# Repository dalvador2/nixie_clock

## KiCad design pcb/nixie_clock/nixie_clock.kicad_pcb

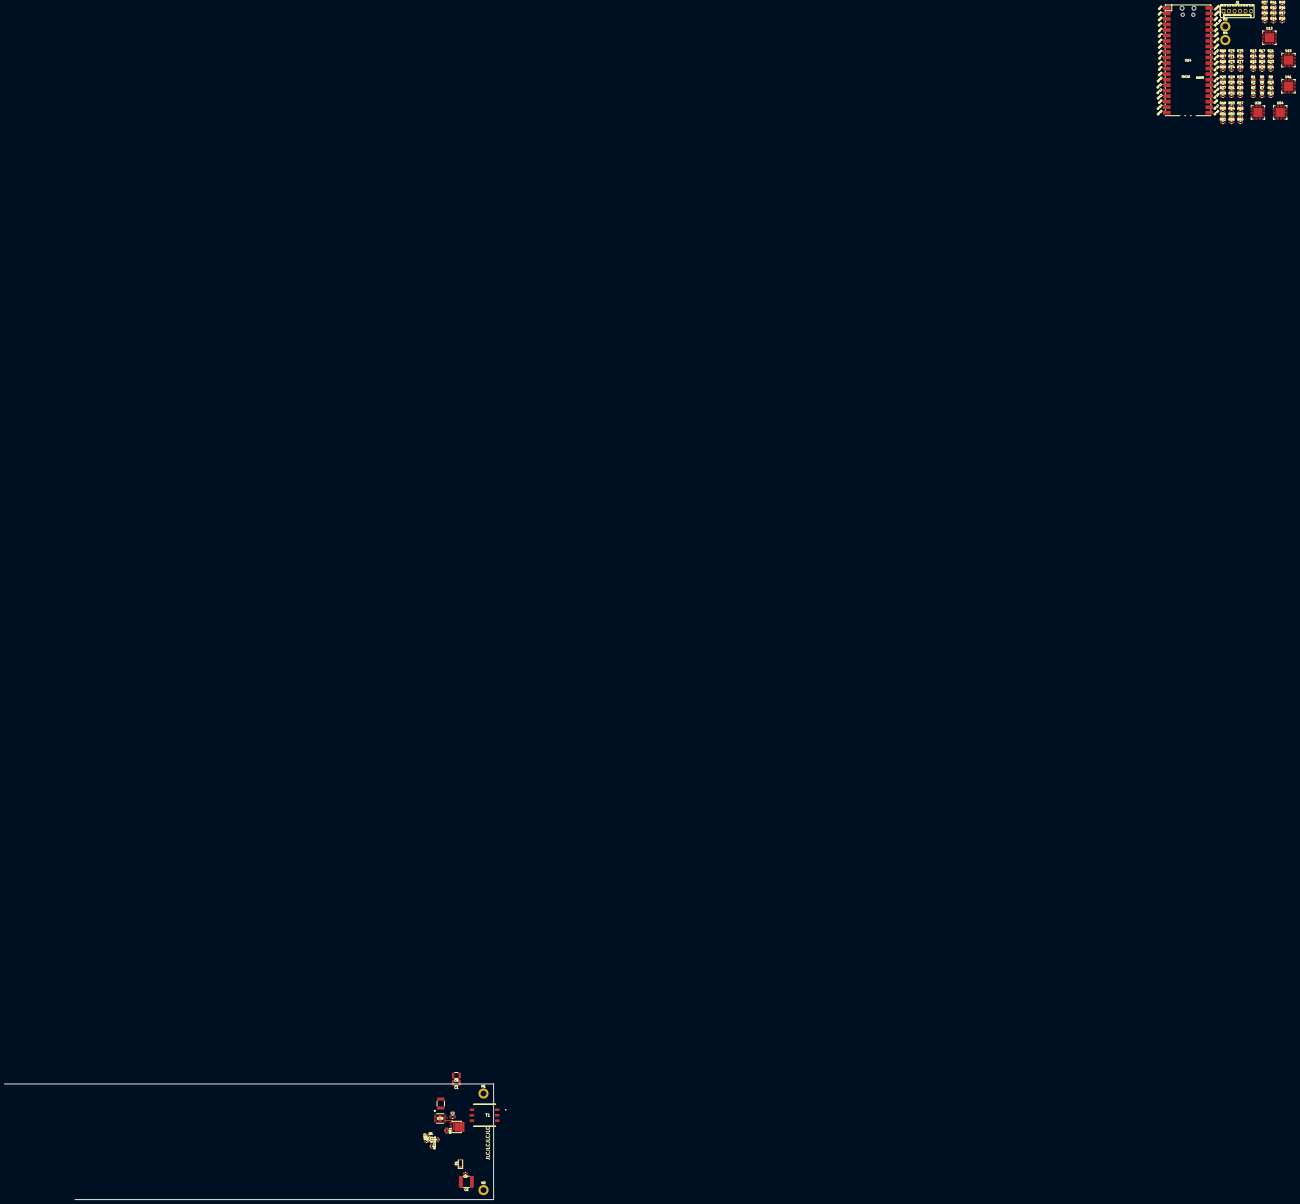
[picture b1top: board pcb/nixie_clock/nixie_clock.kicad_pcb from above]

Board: 6 copper layers, 225.3 x 53.2 mm, 101 parts (0 on the bottom side), 18 nets.

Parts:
C1, C8: 10u; C_1210_3225Metric
C2: 100n; C_0805_2012Metric
C3: 560p; C_0603_1608Metric
C4: 150n; C_0603_1608Metric
C5: 4u7; C_0603_1608Metric
C6: 2u2; C_2220_5750Metric
C7: 100n; C_1812_4532Metric
D1: D; D_SOD-123
H1, H2, H3, H4: MountingHole_Pad; MountingHole_2.7mm_M2.5_DIN965_Pad
J1: Conn_01x06_Pin; Molex_KK-254_AE-6410-06A_1x06_P2.54mm_Vertical
Q1: Q_NMOS_GDS; LFPAK56
R1, R7, R13, R19, R25, R31, R37, R43, R49, R55, R66, R73: 7K87; R_0603_1608Metric
R2, R3, R4, R5, R6, R8, R9, R10, R11, R12, R14, R15, R16, R17, R18, R20, R21, R22, R23, R24, R26, R27, R28, R29, R30, R32, R33, R34, R35, R36, R38, R39, R40, R41, R42, R44, R45, R46, R47, R48, R50, R51, R52, R53, R54, R56, R57, R58, R59, R60, R67, R68, R69, R70, R71, R74, R75, R76, R77, R78: 1K; R_0603_1608Metric
R61: 10m; R_0805_2012Metric
R62: 1M6; R_0603_1608Metric
R63: 13K; R_0603_1608Metric
R64: 20R; R_0603_1608Metric
R65: 300K; R_0603_1608Metric
R72: 86K6; R_0603_1608Metric
T1: 750312367
U13, U15, U28, U41, U54: PCA9685BS; QFN-28-1EP_6x6mm_P0.65mm_EP4.25x4.25mm
U14: PicoW; RPi_PicoW_SMD
U79: LT3759EMSE#TRPBF; MSOP-12_MSE_LIT

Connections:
+3V3: U13.25 (VDD), U13.26 (A0), U13.27 (A1), U14.36 (3V3), U15.25 (VDD), U15.26 (A0), U28.25 (VDD), U28.27 (A1), U41.25 (VDD), U41.28 (A2), U54.25 (VDD), U54.26 (A0), U54.28 (A2)
+5V: C1.1, C2.1, C8.1, T1.6 (SEC_3.3V500MA_2), U14.40 (VBUS), U79.10 (DRIVE), U79.11 (VIN)
+170V: C5.2, C6.2, D1.1 (K), R62.2
/Nixie_Boost/HV_EN: U14.5 (GPIO3), U79.12 (EN/UVLO)
/Nixie_Control/Out_En: U13.20 (~OE), U14.4 (GPIO2), U15.20 (~OE), U28.20 (~OE), U41.20 (~OE), U54.20 (~OE)
/Nixie_Control/SCL: U13.23 (SCL), U14.27 (GPIO21), U15.23 (SCL), U28.23 (SCL), U41.23 (SCL), U54.23 (SCL)
/Nixie_Control/SDA: U13.24 (SDA), U14.26 (GPIO20), U15.24 (SDA), U28.24 (SDA), U41.24 (SDA), U54.24 (SDA)
GND: C1.2, C2.2, C3.2, C4.1, C5.1, C6.1, C7.2, C8.2, H1.1 (1_1), H2.1 (1_1), H3.1 (1_1), H4.1 (1_1), J1.1, J1.2, J1.3, J1.4, J1.5, J1.6, R1.2, R2.2, R3.2, R4.2, R5.2, R6.2, R7.2, R8.2, R9.2, R10.2, R11.2, R12.2, R13.2, R14.2, R15.2, R16.2, R17.2, R18.2, R19.2, R20.2, R21.2, R22.2, R23.2, R24.2, R25.2, R26.2, R27.2, R28.2, R29.2, R30.2, R31.2, R32.2, R33.2, R34.2, R35.2, R36.2, R37.2, R38.2, R39.2, R40.2, R41.2, R42.2, R43.2, R44.2, R45.2, R46.2, R47.2, R48.2, R49.2, R50.2, R51.2, R52.2, R53.2, R54.2, R55.2, R56.2, R57.2, R58.2, R59.2, R60.2, R61.2, R63.1, R66.2, R67.2, R68.2, R69.2, R70.2, R71.2, R72.1, R73.2, R74.2, R75.2, R76.2, R77.2, R78.2, T1.1 (PRI_22-72V_KHZ_1), U13.1 (A3), U13.2 (A4), U13.11 (VSS), U13.21 (A5), U13.22 (EXTCLK), U13.28 (A2), U13.29 (VSS), U14.3 (GND), U14.8 (GND), U14.13 (GND), U14.18 (GND), U14.23 (GND), U14.28 (GND), U14.38 (GND), U15.1 (A3), U15.2 (A4), U15.11 (VSS), U15.21 (A5), U15.22 (EXTCLK), U15.27 (A1), U15.28 (A2), U15.29 (VSS), U28.1 (A3), U28.2 (A4), U28.11 (VSS), U28.21 (A5), U28.22 (EXTCLK), U28.26 (A0), U28.28 (A2), U28.29 (VSS), U41.1 (A3), U41.2 (A4), U41.11 (VSS), U41.21 (A5), U41.22 (EXTCLK), U41.26 (A0), U41.27 (A1), U41.29 (VSS), U54.1 (A3), U54.2 (A4), U54.11 (VSS), U54.21 (A5), U54.22 (EXTCLK), U54.27 (A1), U54.29 (VSS), U79.5 (SYNC), U79.6 (*PGOOD), U79.13 (EPAD)
unnamed: C3.1, R65.1
unnamed: D1.2 (A), T1.3 (PRI_22-72V_KHZ_3)
unnamed: Q1.2 (D), T1.4 (SEC_3.3V500MA_1)
unnamed: Q1.1 (G), R64.2, U79.8 (GATE)
unnamed: Q1.3 (S), R61.1, U79.7 (SENSE)
unnamed: R62.1, R63.2, U79.2 (FBX)
unnamed: C7.1, U79.9 (INTVCC)
unnamed: R72.2, U79.4 (RT)
unnamed: C4.2, U79.3 (SS)
unnamed: R65.2, U79.1 (VC)

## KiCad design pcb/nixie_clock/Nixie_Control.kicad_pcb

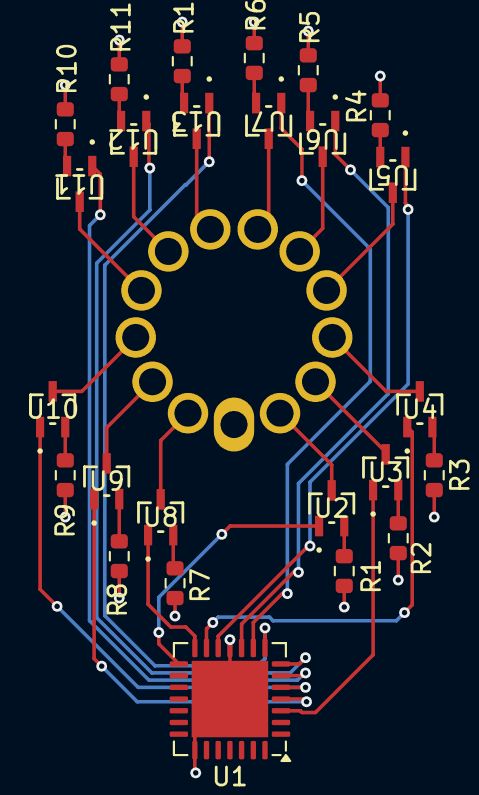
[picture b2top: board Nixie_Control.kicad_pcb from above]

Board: 6 copper layers, 26 parts (1 on the bottom side), 37 nets.

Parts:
R1, R7: 7K87; R_0603_1608Metric
R2, R3, R4, R5, R6, R8, R9, R10, R11, R12: 1K; R_0603_1608Metric
U1: PCA9685BS; QFN-28-1EP_6x6mm_P0.65mm_EP4.25x4.25mm
U2, U3, U4, U5, U6, U7, U8, U9, U10, U11, U12, U13: MSD42WT1G; SOT-323-3_2P2X1P35_ONS
V1: IN14

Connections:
/Nixie_Block2/Cath_0: U1.3 (LED0), U9.1 (BASE)
/Nixie_Block2/Cath_1: U1.4 (LED1), U3.1 (BASE)
/Nixie_Block2/Cath_2: U1.5 (LED2), U4.1 (BASE)
/Nixie_Block2/Cath_3: U1.6 (LED3), U5.1 (BASE)
/Nixie_Block2/Cath_4: U1.7 (LED4), U6.1 (BASE)
/Nixie_Block2/Cath_5: U1.8 (LED5), U7.1 (BASE)
/Nixie_Block2/Cath_6: U1.9 (LED6), U13.1 (BASE)
/Nixie_Block2/Cath_7: U1.10 (LED7), U12.1 (BASE)
/Nixie_Block2/Cath_8: U1.12 (LED8), U11.1 (BASE)
/Nixie_Block2/Cath_9: U1.13 (LED9), U10.1 (BASE)
/Nixie_Block2/Comma_L: U1.14 (LED10), U2.1 (BASE)
/Nixie_Block2/Comma_R: U1.15 (LED11), U8.1 (BASE)
GND: R1.2, R2.2, R3.2, R4.2, R5.2, R6.2, R7.2, R8.2, R9.2, R10.2, R11.2, R12.2, U1.11 (VSS), U1.22 (EXTCLK), U1.29 (VSS)
unnamed: U2.3 (COLLECTOR), V1.13 (Comma_L)
unnamed: R1.1, U2.2 (EMITTER)
unnamed: U3.3 (COLLECTOR), V1.12 (Cath_1)
unnamed: R2.1, U3.2 (EMITTER)
unnamed: U4.3 (COLLECTOR), V1.11 (Cath_2)
unnamed: R3.1, U4.2 (EMITTER)
unnamed: U5.3 (COLLECTOR), V1.10 (Cath_3)
unnamed: R4.1, U5.2 (EMITTER)
unnamed: U6.3 (COLLECTOR), V1.9 (Cath_4)
unnamed: R5.1, U6.2 (EMITTER)
unnamed: U7.3 (COLLECTOR), V1.8 (Cath_5)
unnamed: R6.1, U7.2 (EMITTER)
unnamed: U8.3 (COLLECTOR), V1.2 (Comma_R)
unnamed: R7.1, U8.2 (EMITTER)
unnamed: U9.3 (COLLECTOR), V1.3 (Cath_0)
unnamed: R8.1, U9.2 (EMITTER)
unnamed: U10.3 (COLLECTOR), V1.4 (Cath_9)
unnamed: R9.1, U10.2 (EMITTER)
unnamed: U11.3 (COLLECTOR), V1.5 (Cath_8)
unnamed: R10.1, U11.2 (EMITTER)
unnamed: U12.3 (COLLECTOR), V1.6 (Cath_7)
unnamed: R11.1, U12.2 (EMITTER)
unnamed: U13.3 (COLLECTOR), V1.7 (Cath_6)
unnamed: R12.1, U13.2 (EMITTER)

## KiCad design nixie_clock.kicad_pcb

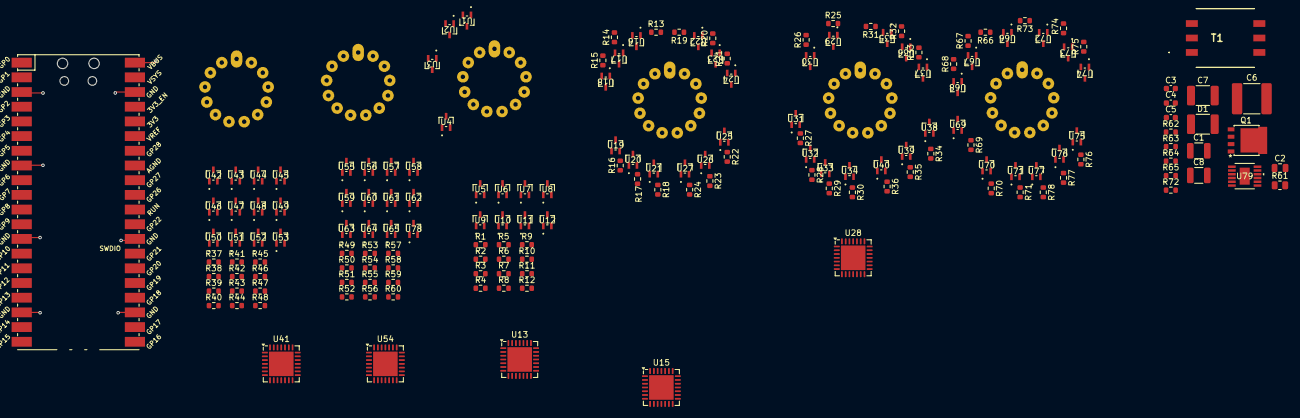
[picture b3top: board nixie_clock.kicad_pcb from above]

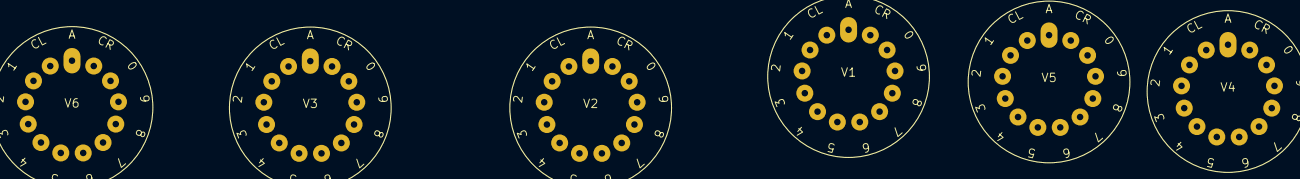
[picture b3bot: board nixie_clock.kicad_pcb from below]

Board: 6 copper layers, 174 parts (6 on the bottom side), 234 nets.

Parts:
C1, C8: 10u; C_1210_3225Metric
C2: 100n; C_0805_2012Metric
C3: 560p; C_0603_1608Metric
C4: 150n; C_0603_1608Metric
C5: 4u7; C_0603_1608Metric
C6: 2u2; C_2220_5750Metric
C7: 100n; C_1812_4532Metric
D1: D; C_1812_4532Metric
Q1: Q_NMOS_GDS; LFPAK56
R1, R7, R13, R19, R25, R31, R37, R43, R49, R55, R66, R73: 7K87; R_0603_1608Metric
R2, R3, R4, R5, R6, R8, R9, R10, R11, R12, R14, R15, R16, R17, R18, R20, R21, R22, R23, R24, R26, R27, R28, R29, R30, R32, R33, R34, R35, R36, R38, R39, R40, R41, R42, R44, R45, R46, R47, R48, R50, R51, R52, R53, R54, R56, R57, R58, R59, R60, R67, R68, R69, R70, R71, R74, R75, R76, R77, R78: 1K; R_0603_1608Metric
R61: 10m; R_0805_2012Metric
R62: 1M6; R_0603_1608Metric
R63: 13K; R_0603_1608Metric
R64: 20R; R_0603_1608Metric
R65: 300K; R_0603_1608Metric
R72: 86K6; R_0603_1608Metric
T1: 750312367
U1, U2, U3, U4, U5, U6, U7, U8, U9, U10, U11, U12, U16, U17, U18, U19, U20, U21, U22, U23, U24, U25, U26, U27, U29, U30, U31, U32, U33, U34, U35, U36, U37, U38, U39, U40, U42, U43, U44, U45, U46, U47, U48, U49, U50, U51, U52, U53, U55, U56, U57, U58, U59, U60, U61, U62, U63, U64, U65, U66, U67, U68, U69, U70, U71, U72, U73, U74, U75, U76, U77, U78: MSD42WT1G; SOT-323-3_2P2X1P35_ONS
U13, U15, U28, U41, U54: PCA9685BS; QFN-28-1EP_6x6mm_P0.65mm_EP4.25x4.25mm
U14: PicoW; RPi_PicoW_SMD
U79: LT3759EMSE-TRPBF; MSOP-12_MSE_LIT
V1, V2, V3, V4, V5, V6: IN14

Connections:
+5V: C1.1, C2.1, C8.1, T1.6 (SEC_3.3V500MA_2), U13.25 (VDD), U13.26 (A0), U14.40 (VBUS), U15.25 (VDD), U15.27 (A1), U28.25 (VDD), U28.26 (A0), U28.27 (A1), U41.25 (VDD), U41.28 (A2), U54.25 (VDD), U54.26 (A0), U54.28 (A2), U79.10 (DRIVE), U79.11 (VIN)
+170V: C5.2, C6.2, D1.1 (K), V1.1 (Anode), V2.1 (Anode), V3.1 (Anode), V4.1 (Anode), V5.1 (Anode), V6.1 (Anode)
/Nixie_Block1/Cath_0: U13.16 (LED12), U67.1 (BASE)
/Nixie_Block1/Cath_1: U13.17 (LED13), U73.1 (BASE)
/Nixie_Block1/Cath_2: U13.18 (LED14), U74.1 (BASE)
/Nixie_Block1/Cath_3: U13.19 (LED15), U75.1 (BASE)
/Nixie_Block1/Cath_4: U15.16 (LED12), U76.1 (BASE)
/Nixie_Block1/Cath_5: U15.17 (LED13), U77.1 (BASE)
/Nixie_Block1/Cath_6: U15.18 (LED14), U71.1 (BASE)
/Nixie_Block1/Cath_7: U15.19 (LED15), U70.1 (BASE)
/Nixie_Block1/Cath_8: U28.16 (LED12), U69.1 (BASE)
/Nixie_Block1/Cath_9: U28.17 (LED13), U68.1 (BASE)
/Nixie_Block1/Comma_L: U28.18 (LED14), U72.1 (BASE)
/Nixie_Block1/Comma_R: U28.19 (LED15), U66.1 (BASE)
/Nixie_Boost/HV_EN: U14.5 (GPIO3), U79.12 (EN/UVLO)
/Nixie_Control1/Nixie_Block2/Cath_0: U15.3 (LED0), U17.1 (BASE)
/Nixie_Control1/Nixie_Block2/Cath_1: U15.4 (LED1), U23.1 (BASE)
/Nixie_Control1/Nixie_Block2/Cath_2: U15.5 (LED2), U24.1 (BASE)
/Nixie_Control1/Nixie_Block2/Cath_3: U15.6 (LED3), U25.1 (BASE)
/Nixie_Control1/Nixie_Block2/Cath_4: U15.7 (LED4), U26.1 (BASE)
/Nixie_Control1/Nixie_Block2/Cath_5: U15.8 (LED5), U27.1 (BASE)
/Nixie_Control1/Nixie_Block2/Cath_6: U15.9 (LED6), U21.1 (BASE)
/Nixie_Control1/Nixie_Block2/Cath_7: U15.10 (LED7), U20.1 (BASE)
/Nixie_Control1/Nixie_Block2/Cath_8: U15.12 (LED8), U19.1 (BASE)
/Nixie_Control1/Nixie_Block2/Cath_9: U15.13 (LED9), U18.1 (BASE)
/Nixie_Control1/Nixie_Block2/Comma_L: U15.14 (LED10), U22.1 (BASE)
/Nixie_Control1/Nixie_Block2/Comma_R: U15.15 (LED11), U16.1 (BASE)
/Nixie_Control2/Nixie_Block2/Cath_0: U28.3 (LED0), U30.1 (BASE)
/Nixie_Control2/Nixie_Block2/Cath_1: U28.4 (LED1), U36.1 (BASE)
/Nixie_Control2/Nixie_Block2/Cath_2: U28.5 (LED2), U37.1 (BASE)
/Nixie_Control2/Nixie_Block2/Cath_3: U28.6 (LED3), U38.1 (BASE)
/Nixie_Control2/Nixie_Block2/Cath_4: U28.7 (LED4), U39.1 (BASE)
/Nixie_Control2/Nixie_Block2/Cath_5: U28.8 (LED5), U40.1 (BASE)
/Nixie_Control2/Nixie_Block2/Cath_6: U28.9 (LED6), U34.1 (BASE)
/Nixie_Control2/Nixie_Block2/Cath_7: U28.10 (LED7), U33.1 (BASE)
/Nixie_Control2/Nixie_Block2/Cath_8: U28.12 (LED8), U32.1 (BASE)
/Nixie_Control2/Nixie_Block2/Cath_9: U28.13 (LED9), U31.1 (BASE)
/Nixie_Control2/Nixie_Block2/Comma_L: U28.14 (LED10), U35.1 (BASE)
/Nixie_Control2/Nixie_Block2/Comma_R: U28.15 (LED11), U29.1 (BASE)
/Nixie_Control3/Nixie_Block2/Cath_0: U41.3 (LED0), U43.1 (BASE)
/Nixie_Control3/Nixie_Block2/Cath_1: U41.4 (LED1), U49.1 (BASE)
/Nixie_Control3/Nixie_Block2/Cath_2: U41.5 (LED2), U50.1 (BASE)
/Nixie_Control3/Nixie_Block2/Cath_3: U41.6 (LED3), U51.1 (BASE)
/Nixie_Control3/Nixie_Block2/Cath_4: U41.7 (LED4), U52.1 (BASE)
/Nixie_Control3/Nixie_Block2/Cath_5: U41.8 (LED5), U53.1 (BASE)
/Nixie_Control3/Nixie_Block2/Cath_6: U41.9 (LED6), U47.1 (BASE)
/Nixie_Control3/Nixie_Block2/Cath_7: U41.10 (LED7), U46.1 (BASE)
/Nixie_Control3/Nixie_Block2/Cath_8: U41.12 (LED8), U45.1 (BASE)
/Nixie_Control3/Nixie_Block2/Cath_9: U41.13 (LED9), U44.1 (BASE)
/Nixie_Control3/Nixie_Block2/Comma_L: U41.14 (LED10), U48.1 (BASE)
/Nixie_Control3/Nixie_Block2/Comma_R: U41.15 (LED11), U42.1 (BASE)
/Nixie_Control4/Nixie_Block2/Cath_0: U54.3 (LED0), U56.1 (BASE)
/Nixie_Control4/Nixie_Block2/Cath_1: U54.4 (LED1), U62.1 (BASE)
/Nixie_Control4/Nixie_Block2/Cath_2: U54.5 (LED2), U63.1 (BASE)
/Nixie_Control4/Nixie_Block2/Cath_3: U54.6 (LED3), U64.1 (BASE)
/Nixie_Control4/Nixie_Block2/Cath_4: U54.7 (LED4), U65.1 (BASE)
/Nixie_Control4/Nixie_Block2/Cath_5: U54.8 (LED5), U78.1 (BASE)
/Nixie_Control4/Nixie_Block2/Cath_6: U54.9 (LED6), U60.1 (BASE)
/Nixie_Control4/Nixie_Block2/Cath_7: U54.10 (LED7), U59.1 (BASE)
/Nixie_Control4/Nixie_Block2/Cath_8: U54.12 (LED8), U58.1 (BASE)
/Nixie_Control4/Nixie_Block2/Cath_9: U54.13 (LED9), U57.1 (BASE)
/Nixie_Control4/Nixie_Block2/Comma_L: U54.14 (LED10), U61.1 (BASE)
/Nixie_Control4/Nixie_Block2/Comma_R: U54.15 (LED11), U55.1 (BASE)
/Nixie_Control/Ext_Clk: U13.20 (~OE), U14.4 (GPIO2), U15.20 (~OE), U28.20 (~OE), U41.20 (~OE), U54.20 (~OE)
/Nixie_Control/Nixie_Block2/Cath_0: U2.1 (BASE), U13.3 (LED0)
/Nixie_Control/Nixie_Block2/Cath_1: U8.1 (BASE), U13.4 (LED1)
/Nixie_Control/Nixie_Block2/Cath_2: U9.1 (BASE), U13.5 (LED2)
/Nixie_Control/Nixie_Block2/Cath_3: U10.1 (BASE), U13.6 (LED3)
/Nixie_Control/Nixie_Block2/Cath_4: U11.1 (BASE), U13.7 (LED4)
/Nixie_Control/Nixie_Block2/Cath_5: U12.1 (BASE), U13.8 (LED5)
/Nixie_Control/Nixie_Block2/Cath_6: U6.1 (BASE), U13.9 (LED6)
/Nixie_Control/Nixie_Block2/Cath_7: U5.1 (BASE), U13.10 (LED7)
/Nixie_Control/Nixie_Block2/Cath_8: U4.1 (BASE), U13.12 (LED8)
/Nixie_Control/Nixie_Block2/Cath_9: U3.1 (BASE), U13.13 (LED9)
/Nixie_Control/Nixie_Block2/Comma_L: U7.1 (BASE), U13.14 (LED10)
/Nixie_Control/Nixie_Block2/Comma_R: U1.1 (BASE), U13.15 (LED11)
/Nixie_Control/SCL: U13.23 (SCL), U14.27 (GPIO21), U15.23 (SCL), U28.23 (SCL), U41.23 (SCL), U54.23 (SCL)
/Nixie_Control/SDA: U13.24 (SDA), U14.26 (GPIO20), U15.24 (SDA), U28.24 (SDA), U41.24 (SDA), U54.24 (SDA)
GND: C1.2, C2.2, C3.2, C4.1, C5.1, C6.1, C7.2, C8.2, R1.2, R2.2, R3.2, R4.2, R5.2, R6.2, R7.2, R8.2, R9.2, R10.2, R11.2, R12.2, R13.2, R14.2, R15.2, R16.2, R17.2, R18.2, R19.2, R20.2, R21.2, R22.2, R23.2, R24.2, R25.2, R26.2, R27.2, R28.2, R29.2, R30.2, R31.2, R32.2, R33.2, R34.2, R35.2, R36.2, R37.2, R38.2, R39.2, R40.2, R41.2, R42.2, R43.2, R44.2, R45.2, R46.2, R47.2, R48.2, R49.2, R50.2, R51.2, R52.2, R53.2, R54.2, R55.2, R56.2, R57.2, R58.2, R59.2, R60.2, R61.2, R63.1, R66.2, R67.2, R68.2, R69.2, R70.2, R71.2, R72.1, R73.2, R74.2, R75.2, R76.2, R77.2, R78.2, T1.1 (PRI_22-72V_KHZ_1), U13.1 (A3), U13.2 (A4), U13.11 (VSS), U13.21 (A5), U13.22 (EXTCLK), U13.27 (A1), U13.28 (A2), U13.29 (VSS), U14.3 (GND), U14.8 (GND), U14.13 (GND), U14.18 (GND), U14.23 (GND), U14.28 (GND), U14.38 (GND), U15.1 (A3), U15.2 (A4), U15.11 (VSS), U15.21 (A5), U15.22 (EXTCLK), U15.26 (A0), U15.28 (A2), U15.29 (VSS), U28.1 (A3), U28.2 (A4), U28.11 (VSS), U28.21 (A5), U28.22 (EXTCLK), U28.28 (A2), U28.29 (VSS), U41.1 (A3), U41.2 (A4), U41.11 (VSS), U41.21 (A5), U41.22 (EXTCLK), U41.26 (A0), U41.27 (A1), U41.29 (VSS), U54.1 (A3), U54.2 (A4), U54.11 (VSS), U54.21 (A5), U54.22 (EXTCLK), U54.27 (A1), U54.29 (VSS), U79.5 (SYNC), U79.6 (*PGOOD), U79.13 (EPAD)
unnamed: C3.1, R65.1
unnamed: D1.2 (A), R62.2, T1.3 (PRI_22-72V_KHZ_3)
unnamed: Q1.2 (D), T1.4 (SEC_3.3V500MA_1)
unnamed: Q1.1 (G), R64.2
unnamed: Q1.3 (S), R61.1, U79.7 (SENSE)
unnamed: U1.3 (COLLECTOR), V1.13 (Comma_R)
unnamed: R1.1, U1.2 (EMITTER)
unnamed: U2.3 (COLLECTOR), V1.12 (Cath_0)
unnamed: R2.1, U2.2 (EMITTER)
unnamed: U3.3 (COLLECTOR), V1.11 (Cath_9)
unnamed: R3.1, U3.2 (EMITTER)
unnamed: U4.3 (COLLECTOR), V1.10 (Cath_8)
unnamed: R4.1, U4.2 (EMITTER)
unnamed: U5.3 (COLLECTOR), V1.9 (Cath_7)
unnamed: R5.1, U5.2 (EMITTER)
unnamed: U6.3 (COLLECTOR), V1.8 (Cath_6)
unnamed: R6.1, U6.2 (EMITTER)
unnamed: U7.3 (COLLECTOR), V1.2 (Comma_L)
unnamed: R7.1, U7.2 (EMITTER)
unnamed: U8.3 (COLLECTOR), V1.3 (Cath_1)
unnamed: R8.1, U8.2 (EMITTER)
unnamed: U9.3 (COLLECTOR), V1.4 (Cath_2)
unnamed: R9.1, U9.2 (EMITTER)
unnamed: U10.3 (COLLECTOR), V1.5 (Cath_3)
unnamed: R10.1, U10.2 (EMITTER)
unnamed: U11.3 (COLLECTOR), V1.6 (Cath_4)
unnamed: R11.1, U11.2 (EMITTER)
unnamed: U12.3 (COLLECTOR), V1.7 (Cath_5)
unnamed: R12.1, U12.2 (EMITTER)
unnamed: U16.3 (COLLECTOR), V2.13 (Comma_R)
unnamed: R13.1, U16.2 (EMITTER)
unnamed: U17.3 (COLLECTOR), V2.12 (Cath_0)
unnamed: R14.1, U17.2 (EMITTER)
unnamed: U18.3 (COLLECTOR), V2.11 (Cath_9)
unnamed: R15.1, U18.2 (EMITTER)
unnamed: U19.3 (COLLECTOR), V2.10 (Cath_8)
unnamed: R16.1, U19.2 (EMITTER)
unnamed: U20.3 (COLLECTOR), V2.9 (Cath_7)
unnamed: R17.1, U20.2 (EMITTER)
unnamed: U21.3 (COLLECTOR), V2.8 (Cath_6)
unnamed: R18.1, U21.2 (EMITTER)
unnamed: U22.3 (COLLECTOR), V2.2 (Comma_L)
unnamed: R19.1, U22.2 (EMITTER)
unnamed: U23.3 (COLLECTOR), V2.3 (Cath_1)
unnamed: R20.1, U23.2 (EMITTER)
unnamed: U24.3 (COLLECTOR), V2.4 (Cath_2)
unnamed: R21.1, U24.2 (EMITTER)
unnamed: U25.3 (COLLECTOR), V2.5 (Cath_3)
unnamed: R22.1, U25.2 (EMITTER)
unnamed: U26.3 (COLLECTOR), V2.6 (Cath_4)
unnamed: R23.1, U26.2 (EMITTER)
unnamed: U27.3 (COLLECTOR), V2.7 (Cath_5)
unnamed: R24.1, U27.2 (EMITTER)
unnamed: U29.3 (COLLECTOR), V3.13 (Comma_R)
unnamed: R25.1, U29.2 (EMITTER)
unnamed: U30.3 (COLLECTOR), V3.12 (Cath_0)
unnamed: R26.1, U30.2 (EMITTER)
unnamed: U31.3 (COLLECTOR), V3.11 (Cath_9)
unnamed: R27.1, U31.2 (EMITTER)
unnamed: U32.3 (COLLECTOR), V3.10 (Cath_8)
unnamed: R28.1, U32.2 (EMITTER)
unnamed: U33.3 (COLLECTOR), V3.9 (Cath_7)
unnamed: R29.1, U33.2 (EMITTER)
unnamed: U34.3 (COLLECTOR), V3.8 (Cath_6)
unnamed: R30.1, U34.2 (EMITTER)
unnamed: U35.3 (COLLECTOR), V3.2 (Comma_L)
unnamed: R31.1, U35.2 (EMITTER)
unnamed: U36.3 (COLLECTOR), V3.3 (Cath_1)
unnamed: R32.1, U36.2 (EMITTER)
unnamed: U37.3 (COLLECTOR), V3.4 (Cath_2)
unnamed: R33.1, U37.2 (EMITTER)
unnamed: U38.3 (COLLECTOR), V3.5 (Cath_3)
unnamed: R34.1, U38.2 (EMITTER)
unnamed: U39.3 (COLLECTOR), V3.6 (Cath_4)
unnamed: R35.1, U39.2 (EMITTER)
unnamed: U40.3 (COLLECTOR), V3.7 (Cath_5)
unnamed: R36.1, U40.2 (EMITTER)
unnamed: U42.3 (COLLECTOR), V4.13 (Comma_R)
unnamed: R37.1, U42.2 (EMITTER)
unnamed: U43.3 (COLLECTOR), V4.12 (Cath_0)
unnamed: R38.1, U43.2 (EMITTER)
unnamed: U44.3 (COLLECTOR), V4.11 (Cath_9)
unnamed: R39.1, U44.2 (EMITTER)
unnamed: U45.3 (COLLECTOR), V4.10 (Cath_8)
unnamed: R40.1, U45.2 (EMITTER)
unnamed: U46.3 (COLLECTOR), V4.9 (Cath_7)
unnamed: R41.1, U46.2 (EMITTER)
unnamed: U47.3 (COLLECTOR), V4.8 (Cath_6)
unnamed: R42.1, U47.2 (EMITTER)
unnamed: U48.3 (COLLECTOR), V4.2 (Comma_L)
unnamed: R43.1, U48.2 (EMITTER)
unnamed: U49.3 (COLLECTOR), V4.3 (Cath_1)
unnamed: R44.1, U49.2 (EMITTER)
unnamed: U50.3 (COLLECTOR), V4.4 (Cath_2)
unnamed: R45.1, U50.2 (EMITTER)
unnamed: U51.3 (COLLECTOR), V4.5 (Cath_3)
unnamed: R46.1, U51.2 (EMITTER)
unnamed: U52.3 (COLLECTOR), V4.6 (Cath_4)
unnamed: R47.1, U52.2 (EMITTER)
unnamed: U53.3 (COLLECTOR), V4.7 (Cath_5)
unnamed: R48.1, U53.2 (EMITTER)
unnamed: U55.3 (COLLECTOR), V5.13 (Comma_R)
unnamed: R49.1, U55.2 (EMITTER)
unnamed: U56.3 (COLLECTOR), V5.12 (Cath_0)
unnamed: R50.1, U56.2 (EMITTER)
unnamed: U57.3 (COLLECTOR), V5.11 (Cath_9)
unnamed: R51.1, U57.2 (EMITTER)
unnamed: U58.3 (COLLECTOR), V5.10 (Cath_8)
unnamed: R52.1, U58.2 (EMITTER)
unnamed: U59.3 (COLLECTOR), V5.9 (Cath_7)
unnamed: R53.1, U59.2 (EMITTER)
unnamed: U60.3 (COLLECTOR), V5.8 (Cath_6)
unnamed: R54.1, U60.2 (EMITTER)
unnamed: U61.3 (COLLECTOR), V5.2 (Comma_L)
unnamed: R55.1, U61.2 (EMITTER)
unnamed: U62.3 (COLLECTOR), V5.3 (Cath_1)
unnamed: R56.1, U62.2 (EMITTER)
unnamed: U63.3 (COLLECTOR), V5.4 (Cath_2)
unnamed: R57.1, U63.2 (EMITTER)
unnamed: U64.3 (COLLECTOR), V5.5 (Cath_3)
unnamed: R58.1, U64.2 (EMITTER)
unnamed: U65.3 (COLLECTOR), V5.6 (Cath_4)
unnamed: R59.1, U65.2 (EMITTER)
unnamed: U66.3 (COLLECTOR), V6.13 (Comma_R)
unnamed: R66.1, U66.2 (EMITTER)
unnamed: U67.3 (COLLECTOR), V6.12 (Cath_0)
unnamed: R67.1, U67.2 (EMITTER)
unnamed: U68.3 (COLLECTOR), V6.11 (Cath_9)
unnamed: R68.1, U68.2 (EMITTER)
unnamed: U69.3 (COLLECTOR), V6.10 (Cath_8)
unnamed: R69.1, U69.2 (EMITTER)
unnamed: U70.3 (COLLECTOR), V6.9 (Cath_7)
unnamed: R70.1, U70.2 (EMITTER)
unnamed: U71.3 (COLLECTOR), V6.8 (Cath_6)
unnamed: R71.1, U71.2 (EMITTER)
unnamed: U72.3 (COLLECTOR), V6.2 (Comma_L)
unnamed: R73.1, U72.2 (EMITTER)
unnamed: U73.3 (COLLECTOR), V6.3 (Cath_1)
unnamed: R74.1, U73.2 (EMITTER)
unnamed: U74.3 (COLLECTOR), V6.4 (Cath_2)
unnamed: R75.1, U74.2 (EMITTER)
unnamed: U75.3 (COLLECTOR), V6.5 (Cath_3)
unnamed: R76.1, U75.2 (EMITTER)
unnamed: U76.3 (COLLECTOR), V6.6 (Cath_4)
unnamed: R77.1, U76.2 (EMITTER)
unnamed: U77.3 (COLLECTOR), V6.7 (Cath_5)
unnamed: R78.1, U77.2 (EMITTER)
unnamed: U78.3 (COLLECTOR), V5.7 (Cath_5)
unnamed: R60.1, U78.2 (EMITTER)
unnamed: R62.1, R63.2, U79.2 (FBX)
unnamed: R64.1, U79.8 (GATE)
unnamed: C7.1, U79.9 (INTVCC)
unnamed: R72.2, U79.4 (RT)
unnamed: C4.2, U79.3 (SS)
unnamed: R65.2, U79.1 (VC)

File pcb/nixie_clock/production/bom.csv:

Designator,Footprint,Quantity,Value,LCSC Part #
"C1, C8",1210,2,10u,C6477141
C2,0805,1,100n,C2170365
C3,0603,1,560p,C2171678
C4,0603,1,150n,C3844381
C5,0603,1,4u7,C3842329
C6,2220,1,2u2,C2168251
C7,1812,1,100n,C2179130
D1,D_SOD-123,1,D,C17550678
Q1,LFPAK56,1,Q_NMOS_GDS,C3282674
"R1, R13, R19, R25, R31, R37, R43, R49, R55, R66, R7, R73",0603,12,7K87,C137680
"R10, R11, R12, R14, R15, R16, R17, R18, R2, R20, R21, R22, R23, R24, R26, R27, R28, R29, R3, R30, R32, R33, R34, R35, R36, R38, R39, R4, R40, R41, R42, R44, R45, R46, R47, R48, R5, R50, R51, R52, R53, R54, R56, R57, R58, R59, R6, R60, R67, R68, R69, R70, R71, R74, R75, R76, R77, R78, R8, R9",0603,60,1K,C22548
R61,0805,1,10m,C2977779
R62,0603,1,1M6,C2091296
R63,0603,1,13K,C402966
R64,0603,1,20R,C400657
R65,0603,1,300K,C278615
R72,0603,1,86K6,C2094634
"S1, S2, S3",SW_SKRTLAE010,3,SKRTLAE010,C110293
T1,750312367,1,750312367,C17357180
"U1, U10, U11, U12, U16, U17, U18, U19, U2, U20, U21, U22, U23, U24, U25, U26, U27, U29, U3, U30, U31, U32, U33, U34, U35, U36, U37, U38, U39, U4, U40, U42, U43, U44, U45, U46, U47, U48, U49, U5, U50, U51, U52, U53, U55, U56, U57, U58, U59, U6, U60, U61, U62, U63, U64, U65, U66, U67, U68, U69, U7, U70, U71, U72, U73, U74, U75, U76, U77, U78, U8, U9",SOT-323-3_2P2X1P35_ONS,72,MSD42WT1G,C891781
"U13, U15, U28, U41, U54",QFN-28-1EP_6x6mm_P0.65mm_EP4.25x4.25mm,5,PCA9685BS,C5191634
U79,MSOP-12_MSE_LIT,1,LT3759EMSE#TRPBF,C580139

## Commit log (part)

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2024-09-27 nixie cad add
2024-09-27 initial stages of clock design and parts list creation
2024-10-20 pcb layout nixie tube wiring
2024-10-21 nixie pin changes and more wiring
2024-10-22 remove busses and output stuff
2024-10-29 schematic finalisation, footprint assignment and start on placeing components in layout.
2024-11-01 finalization of schematic (might add fuze on 170v supply) looking at pcb routing now. Decided on 6 layers.
2024-11-02 hierarkical pcb switch and finishing of layout time for final checks need to redo nixie tube layout
2024-11-03 3d models done
2024-11-07 fixing some issues.
2024-11-07 added grounding
2024-11-19 changes and improvements
2024-12-10 final commits before sending to jlc
2025-01-02 pcb final changes or lock files
2025-02-11 pcb changes and breakages need to fix later
2025-02-21 comma and digit display functions fully functional
2025-03-11 now communicating
2025-03-24 fix pcb to correct and first steps on a menu
2025-03-24 updated to kicad9
